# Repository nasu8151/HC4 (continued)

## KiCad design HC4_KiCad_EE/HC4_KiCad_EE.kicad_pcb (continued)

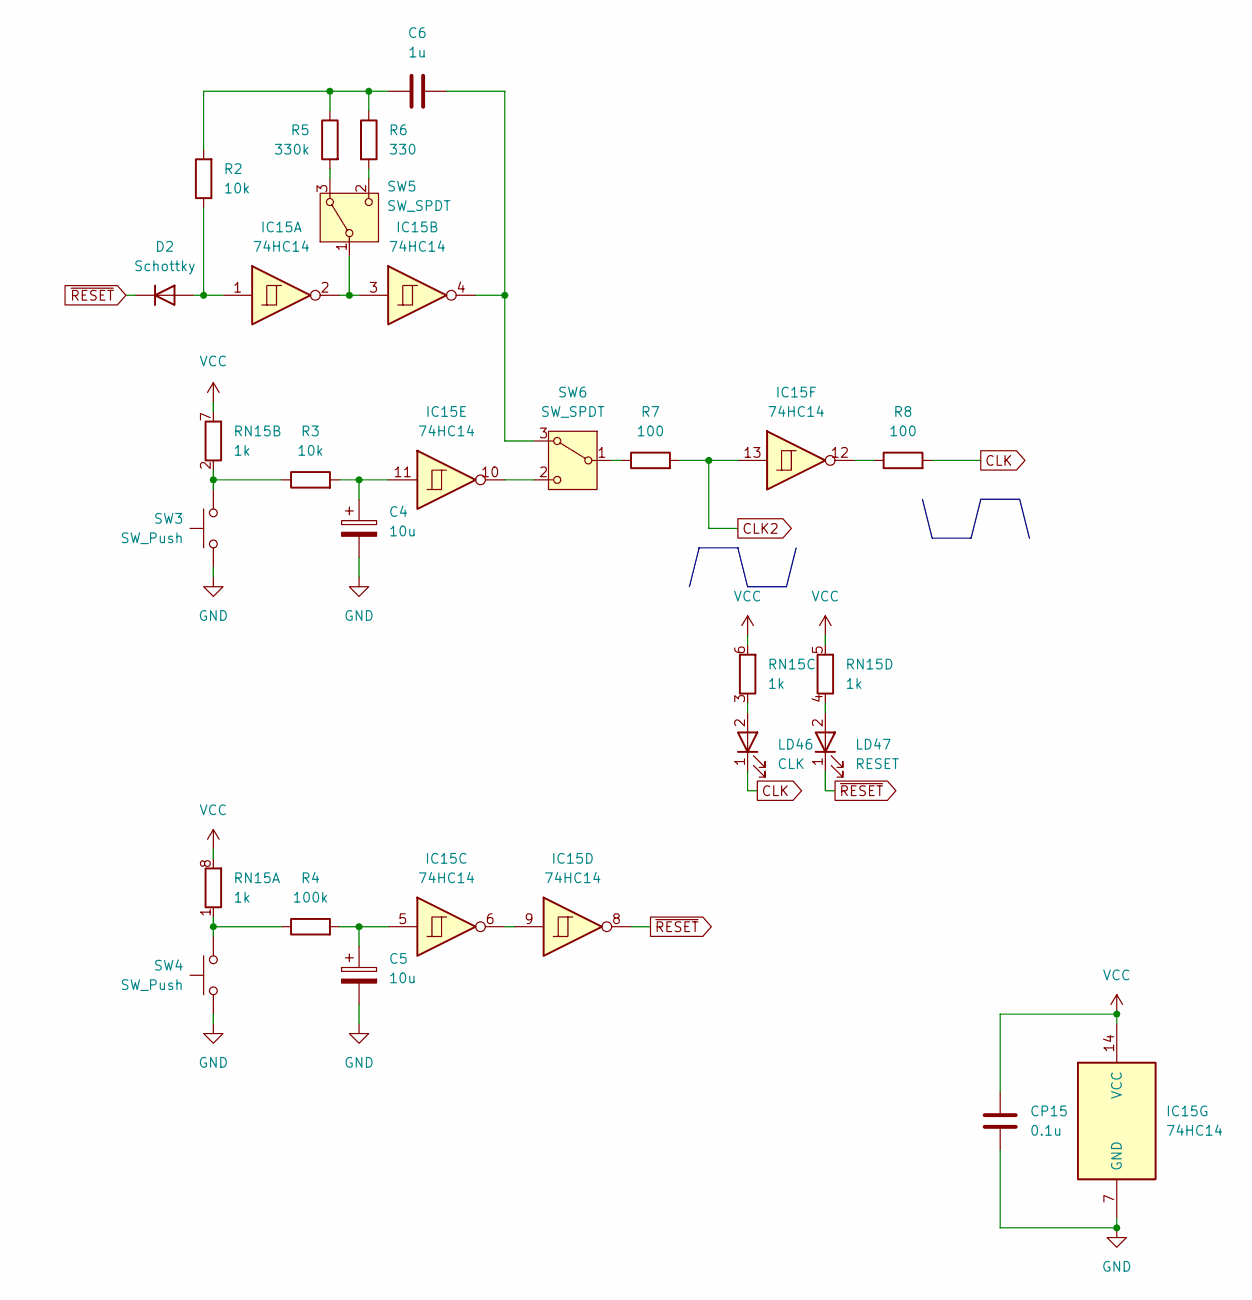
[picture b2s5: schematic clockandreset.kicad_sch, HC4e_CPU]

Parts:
C4, C5: 10u; CP_Radial_D5.0mm_P2.50mm
C6: 1u; C_Radial_D5.0mm_H5.0mm_P2.00mm
CP15: 0.1u; C_0603_1608Metric; LCSC PN C14663
D2: Schottky; D_SOD-323_HandSoldering
IC15: 74HC14; SO-14_5.3x10.2mm_P1.27mm
LD46: CLK; LED_D5.0mm
LD47: RESET; LED_D5.0mm
R2, R3: 10k; R_0603_1608Metric; LCSC PN C25804
R4: 100k; R_0603_1608Metric; LCSC PN C25803
R5: 330k; R_0603_1608Metric; LCSC PN C23137
R6: 330; R_0603_1608Metric; LCSC PN C23151
R7, R8: 100; R_0603_1608Metric; LCSC PN C22775
RN15: 1k; R_Array_Convex_4x0603; LCSC PN C20197
SW3, SW4: SW_Push; SW_PUSH_6mm
SW5, SW6: SW_SPDT; SW_Slide-03_Wuerth-WS-SLTV_10x2.5x6.4_P2.54mm

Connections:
CLK: LD46.1 (K_1), R8.2; also elsewhere on the board
CLK2: IC15.13, R7.2; also elsewhere on the board
GND: C4.2, C5.2, CP15.2, IC15.7 (GND), SW3.1, SW4.1; also elsewhere on the board
unnamed: C4.1, IC15.11, R3.2
unnamed: C5.1, IC15.5, R4.2
unnamed: C6.1, R2.2, R5.1, R6.1
unnamed: D2.2 (A), IC15.1, R2.1
unnamed: IC15.6, IC15.9
unnamed: IC15.12, R8.1
unnamed: R4.1, RN15.1 (R1.1), SW4.2
unnamed: R3.1, RN15.2 (R2.1), SW3.2
unnamed: LD46.2, RN15.3 (R3.1)
unnamed: LD47.2, RN15.4 (R4.1)
unnamed: R5.2, SW5.3 (A)
unnamed: IC15.2, IC15.3, SW5.1 (B)
unnamed: R6.2, SW5.2 (C)
unnamed: C6.2, IC15.4, SW6.3 (A)
unnamed: R7.1, SW6.1 (B)
unnamed: IC15.10, SW6.2 (C)
VCC: CP15.1, IC15.14 (VCC), RN15.5 (R4.2), RN15.6 (R3.2), RN15.7 (R2.2), RN15.8 (R1.2); also elsewhere on the board
~RESET: D2.1 (K), IC15.8, LD47.1 (K_1); also elsewhere on the board

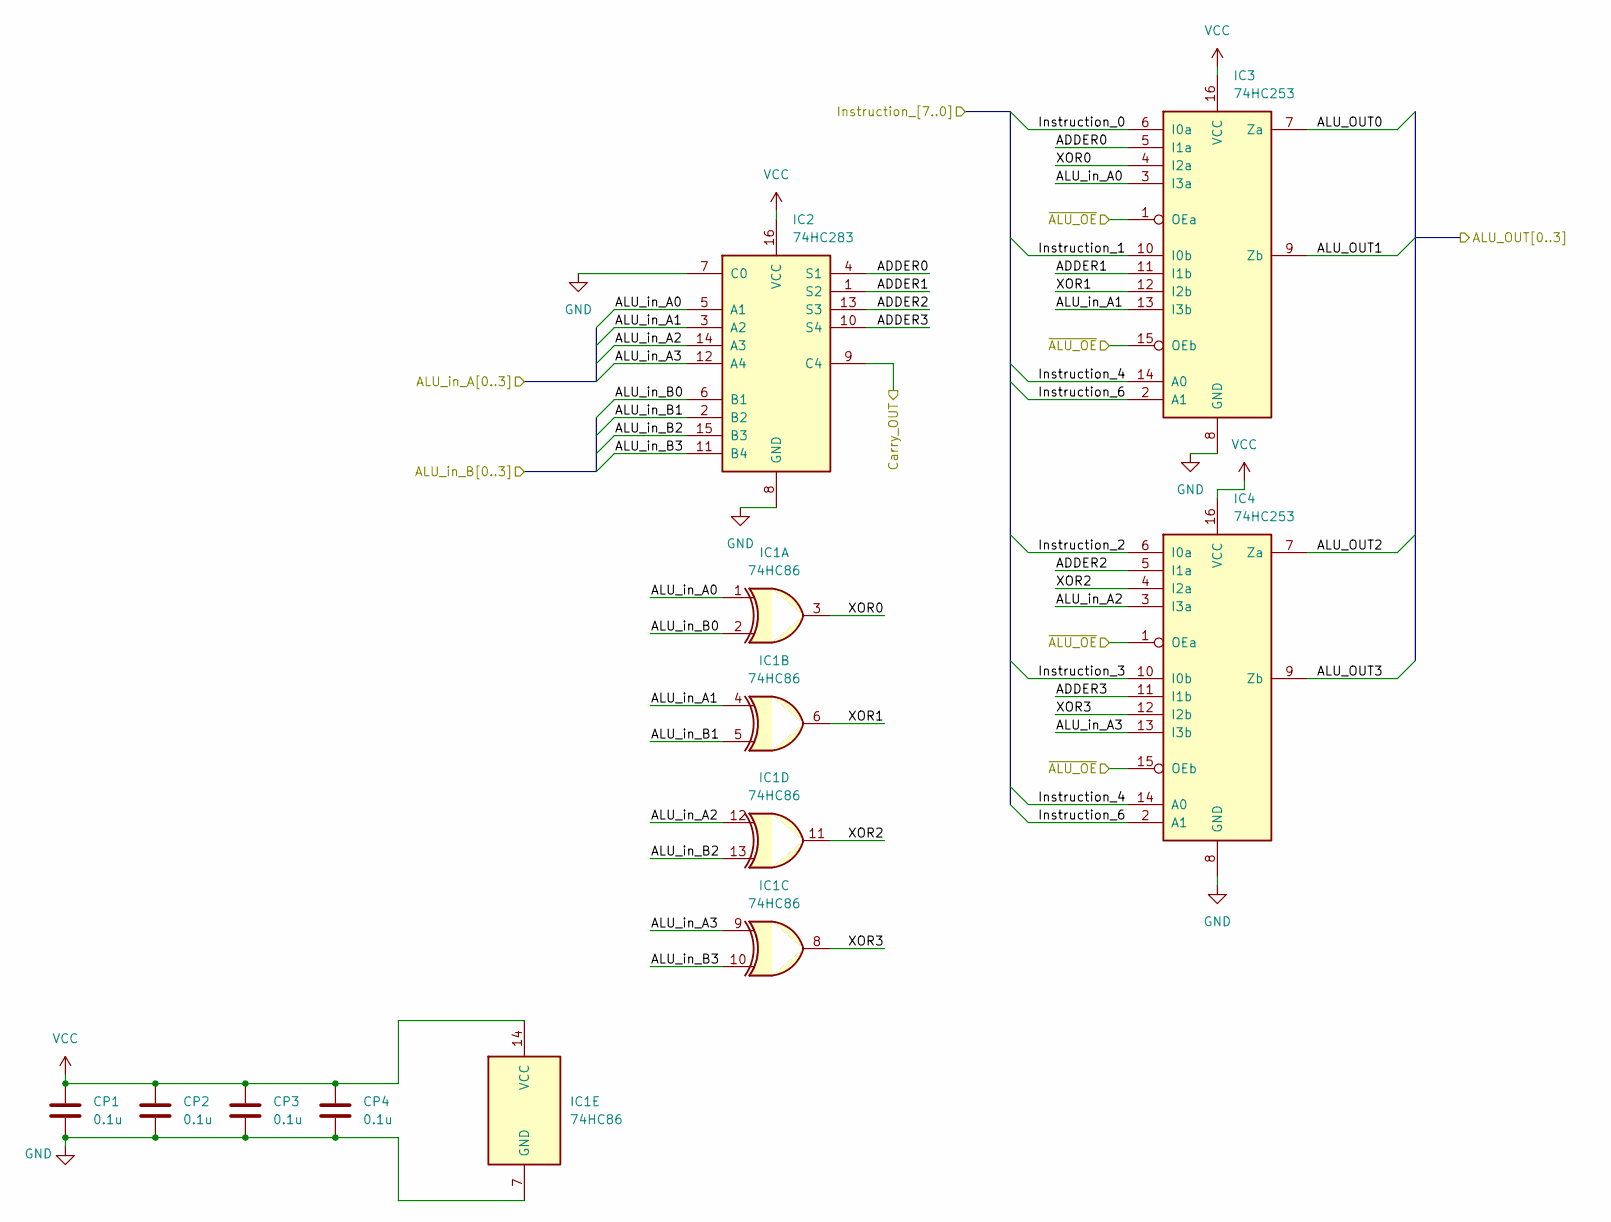
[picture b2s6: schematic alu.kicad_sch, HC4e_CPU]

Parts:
CP1, CP2, CP3, CP4: 0.1u; C_0603_1608Metric; LCSC PN C14663
IC1: 74HC86; SO-14_5.3x10.2mm_P1.27mm
IC2: 74HC283; SO-16_5.3x10.2mm_P1.27mm
IC3, IC4: 74HC253; SO-16_5.3x10.2mm_P1.27mm

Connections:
/ALU/ADDER0: IC2.4 (S1), IC3.5 (I1a)
/ALU/ADDER1: IC2.1 (S2), IC3.11 (I1b)
/ALU/ADDER2: IC2.13 (S3), IC4.5 (I1a)
/ALU/ADDER3: IC2.10 (S4), IC4.11 (I1b)
/ALU/ALU_OUT0: IC3.7 (Za); also elsewhere on the board
/ALU/ALU_OUT1: IC3.9 (Zb); also elsewhere on the board
/ALU/ALU_OUT2: IC4.7 (Za); also elsewhere on the board
/ALU/ALU_OUT3: IC4.9 (Zb); also elsewhere on the board
/ALU/ALU_in_A0: IC1.1, IC2.5 (A1), IC3.3 (I3a); also elsewhere on the board
/ALU/ALU_in_A1: IC1.4, IC2.3 (A2), IC3.13 (I3b); also elsewhere on the board
/ALU/ALU_in_A2: IC1.12, IC2.14 (A3), IC4.3 (I3a); also elsewhere on the board
/ALU/ALU_in_A3: IC1.9, IC2.12 (A4), IC4.13 (I3b); also elsewhere on the board
/ALU/ALU_in_B0: IC1.2, IC2.6 (B1); also elsewhere on the board
/ALU/ALU_in_B1: IC1.5, IC2.2 (B2); also elsewhere on the board
/ALU/ALU_in_B2: IC1.13, IC2.15 (B3); also elsewhere on the board
/ALU/ALU_in_B3: IC1.10, IC2.11 (B4); also elsewhere on the board
/ALU/Carry_OUT: IC2.9 (C4); also elsewhere on the board
/ALU/Instruction_4: IC3.14 (A0), IC4.14 (A0); also elsewhere on the board
/ALU/Instruction_6: IC3.2 (A1), IC4.2 (A1); also elsewhere on the board
/ALU/XOR0: IC1.3, IC3.4 (I2a)
/ALU/XOR1: IC1.6, IC3.12 (I2b)
/ALU/XOR2: IC1.11, IC4.4 (I2a)
/ALU/XOR3: IC1.8, IC4.12 (I2b)
/Instruction Decoder/READ: IC3.1 (OEa), IC3.15 (OEb), IC4.1 (OEa), IC4.15 (OEb); also elsewhere on the board
GND: CP1.2, CP2.2, CP3.2, CP4.2, IC1.7 (GND), IC2.7 (C0), IC2.8 (GND), IC3.8 (GND), IC4.8 (GND); also elsewhere on the board
VCC: CP1.1, CP2.1, CP3.1, CP4.1, IC1.14 (VCC), IC2.16 (VCC), IC3.16 (VCC), IC4.16 (VCC); also elsewhere on the board

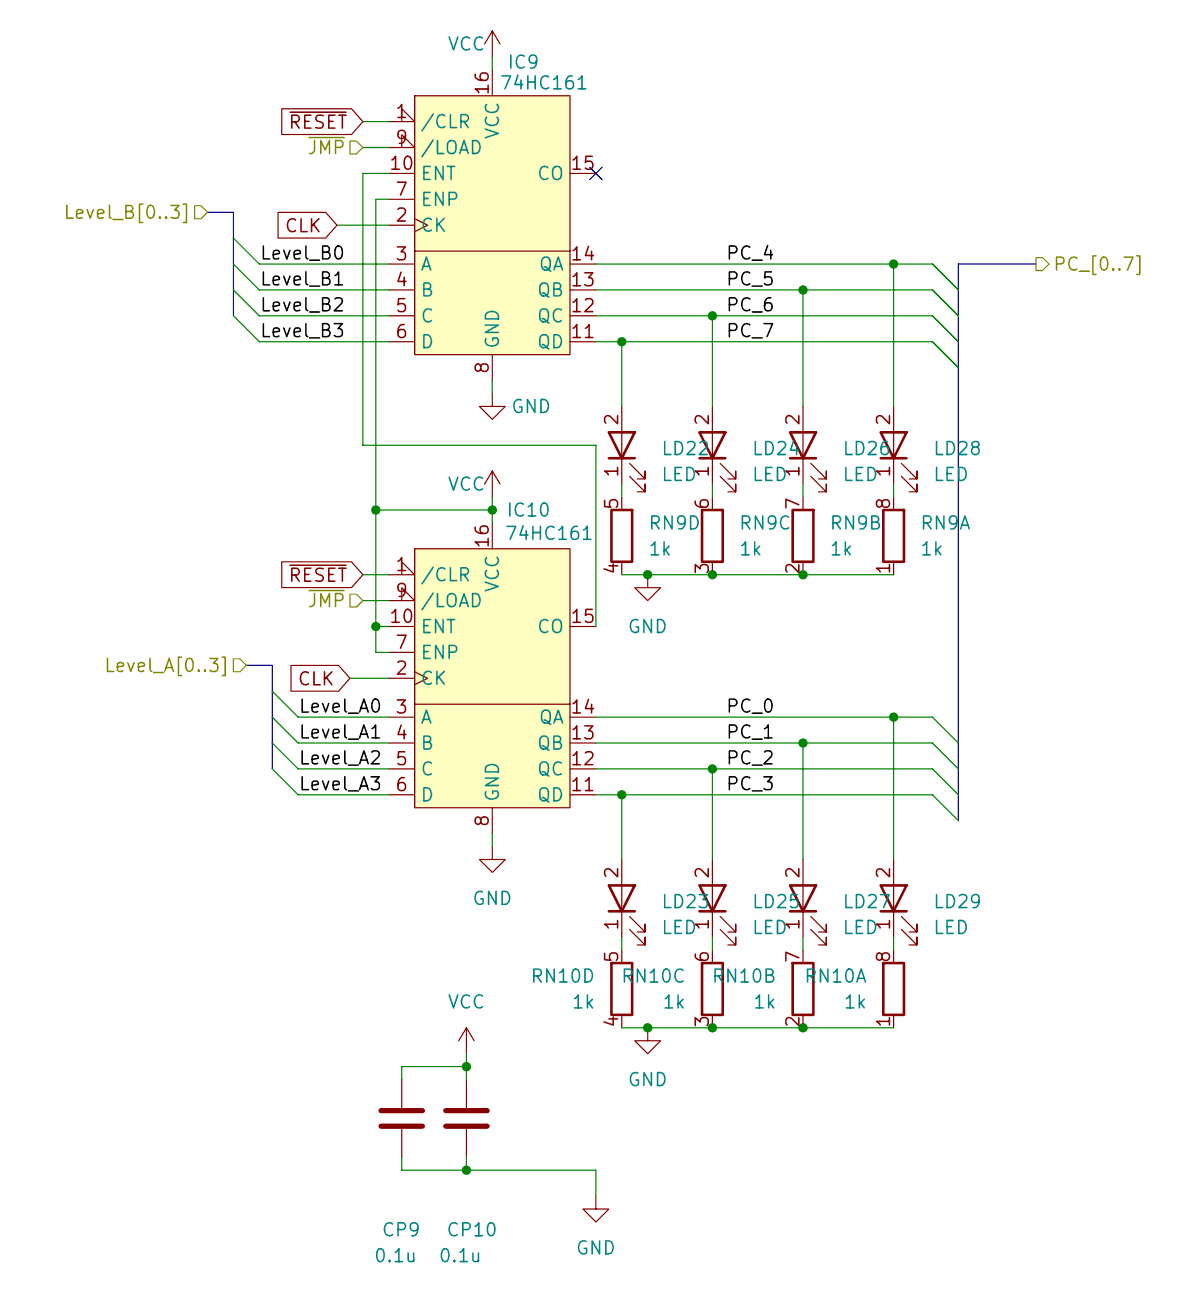
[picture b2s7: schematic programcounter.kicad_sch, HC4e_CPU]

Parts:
CP9, CP10: 0.1u; C_0603_1608Metric; LCSC PN C14663
IC9, IC10: 74HC161; SO-16_5.3x10.2mm_P1.27mm
LD22, LD23, LD24, LD25, LD26, LD27, LD28, LD29: LED; LED_Rectangular_W5.0mm_H2.0mm
RN9, RN10: 1k; R_Array_Convex_4x0603; LCSC PN C20197

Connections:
/ALU/ALU_in_A0: IC10.3 (A); also elsewhere on the board
/ALU/ALU_in_A1: IC10.4 (B); also elsewhere on the board
/ALU/ALU_in_A2: IC10.5 (C); also elsewhere on the board
/ALU/ALU_in_A3: IC10.6 (D); also elsewhere on the board
/ALU/ALU_in_B0: IC9.3 (A); also elsewhere on the board
/ALU/ALU_in_B1: IC9.4 (B); also elsewhere on the board
/ALU/ALU_in_B2: IC9.5 (C); also elsewhere on the board
/ALU/ALU_in_B3: IC9.6 (D); also elsewhere on the board
/Instruction Decoder/~JMP: IC9.9 (/LOAD), IC10.9 (/LOAD); also elsewhere on the board
/Program Counter/PC_0: IC10.14 (QA), LD29.2; also elsewhere on the board
/Program Counter/PC_1: IC10.13 (QB), LD27.2; also elsewhere on the board
/Program Counter/PC_2: IC10.12 (QC), LD25.2; also elsewhere on the board
/Program Counter/PC_3: IC10.11 (QD), LD23.2; also elsewhere on the board
/Program Counter/PC_4: IC9.14 (QA), LD28.2; also elsewhere on the board
/Program Counter/PC_5: IC9.13 (QB), LD26.2; also elsewhere on the board
/Program Counter/PC_6: IC9.12 (QC), LD24.2; also elsewhere on the board
/Program Counter/PC_7: IC9.11 (QD), LD22.2; also elsewhere on the board
CLK: IC9.2 (CK), IC10.2 (CK); also elsewhere on the board
GND: CP9.2, CP10.2, IC9.8 (GND), IC10.8 (GND), RN9.1 (R1.1), RN9.2 (R2.1), RN9.3 (R3.1), RN9.4 (R4.1), RN10.1 (R1.1), RN10.2 (R2.1), RN10.3 (R3.1), RN10.4 (R4.1); also elsewhere on the board
unnamed: IC9.10 (ENT), IC10.15 (CO)
unnamed: LD22.1 (K_1), RN9.5 (R4.2)
unnamed: LD23.1 (K_1), RN10.5 (R4.2)
unnamed: LD24.1 (K_1), RN9.6 (R3.2)
unnamed: LD25.1 (K_1), RN10.6 (R3.2)
unnamed: LD26.1 (K_1), RN9.7 (R2.2)
unnamed: LD27.1 (K_1), RN10.7 (R2.2)
unnamed: LD28.1 (K_1), RN9.8 (R1.2)
unnamed: LD29.1 (K_1), RN10.8 (R1.2)
VCC: CP9.1, CP10.1, IC9.7 (ENP), IC9.16 (VCC), IC10.7 (ENP), IC10.10 (ENT), IC10.16 (VCC); also elsewhere on the board
~RESET: IC9.1 (/CLR), IC10.1 (/CLR); also elsewhere on the board

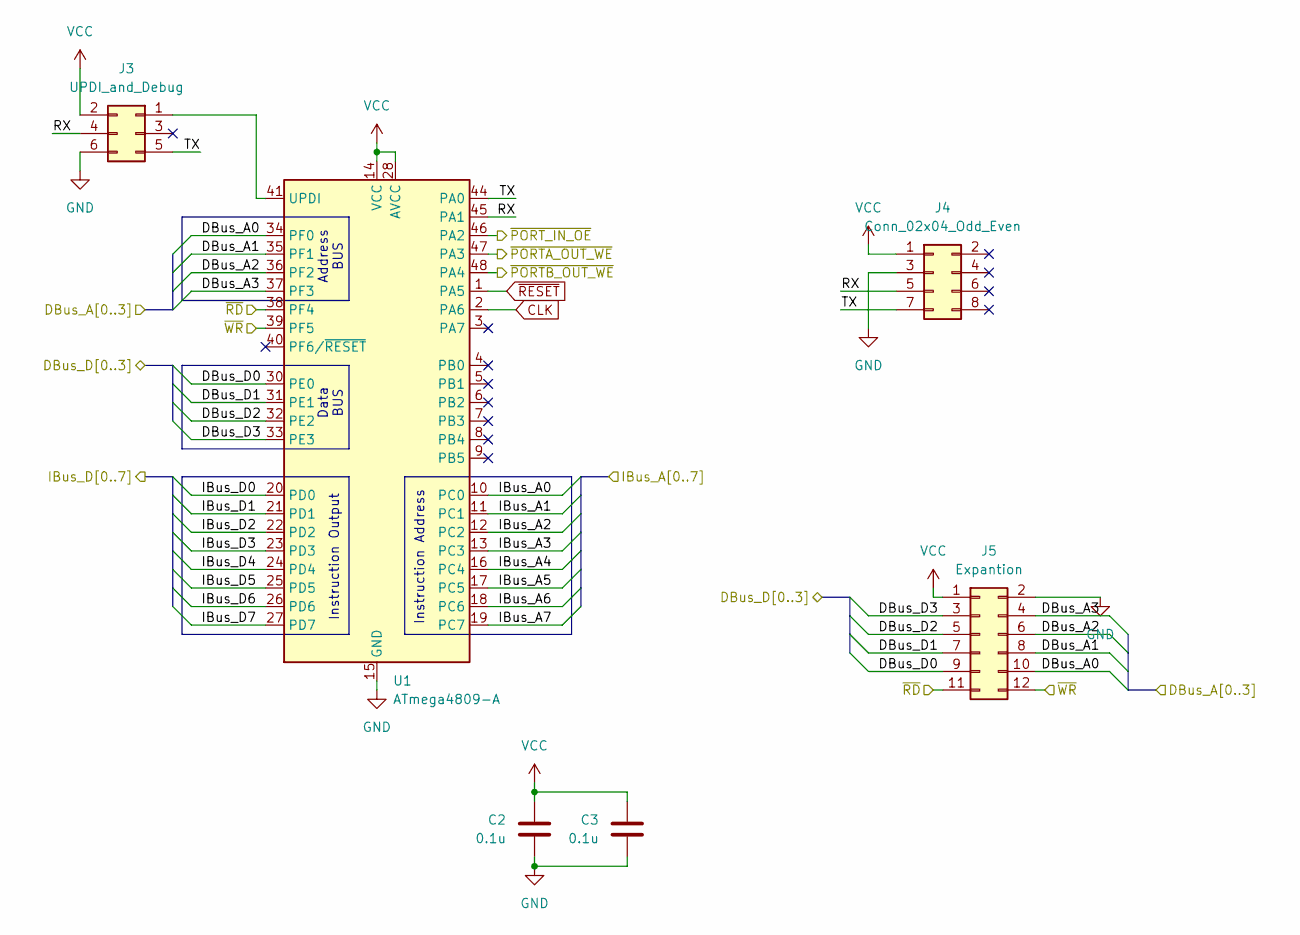
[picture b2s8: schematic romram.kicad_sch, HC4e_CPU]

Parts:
C2, C3: 0.1u; C_0603_1608Metric; LCSC PN C14663
J3: UPDI_and_Debug; PinHeader_2x03_P2.54mm_Vertical
J4: Conn_02x04_Odd_Even; PinHeader_2x04_P2.54mm_Vertical
J5: Expantion; PinHeader_2x06_P2.54mm_Vertical
U1: ATmega4809-A; TQFP-48_7x7mm_P0.5mm; LCSC PN C1340574

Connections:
/ALU/ALU_OUT0: J5.9, U1.30 (PE0); also elsewhere on the board
/ALU/ALU_OUT1: J5.7, U1.31 (PE1); also elsewhere on the board
/ALU/ALU_OUT2: J5.5, U1.32 (PE2); also elsewhere on the board
/ALU/ALU_OUT3: J5.3, U1.33 (PE3); also elsewhere on the board
/ALU/Instruction_4: U1.24 (PD4); also elsewhere on the board
/ALU/Instruction_5: U1.25 (PD5); also elsewhere on the board
/ALU/Instruction_6: U1.26 (PD6); also elsewhere on the board
/ALU/Instruction_7: U1.27 (PD7); also elsewhere on the board
/Data BUS/~IN_PORT_OE: U1.46 (PA2); also elsewhere on the board
/Data BUS/~PORTA_OUT_WE: U1.47 (PA3); also elsewhere on the board
/Data BUS/~PORTB_OUT_WE: U1.48 (PA4); also elsewhere on the board
/Instruction Decoder/~RAM_RD: J5.11, U1.38 (PF4); also elsewhere on the board
/Instruction Decoder/~RAM_WR: J5.12, U1.39 (PF5); also elsewhere on the board
/Program Counter/PC_0: U1.10 (PC0); also elsewhere on the board
/Program Counter/PC_1: U1.11 (PC1); also elsewhere on the board
/Program Counter/PC_2: U1.12 (PC2); also elsewhere on the board
/Program Counter/PC_3: U1.13 (PC3); also elsewhere on the board
/Program Counter/PC_4: U1.16 (PC4); also elsewhere on the board
/Program Counter/PC_5: U1.17 (PC5); also elsewhere on the board
/Program Counter/PC_6: U1.18 (PC6); also elsewhere on the board
/Program Counter/PC_7: U1.19 (PC7); also elsewhere on the board
/ROM_RAM/RX: J3.4, J4.5, U1.45 (PA1)
/ROM_RAM/TX: J3.5, J4.7, U1.44 (PA0)
CLK: U1.2 (PA6); also elsewhere on the board
GND: C2.2, C3.2, J3.6, J4.3, J5.2, U1.15 (GND), U1.29 (GND), U1.43 (GND); also elsewhere on the board
unnamed: J3.1, U1.41 (UPDI)
VCC: C2.1, C3.1, J3.2, J4.1, J5.1, U1.14 (VCC), U1.28 (AVCC), U1.42 (VCC); also elsewhere on the board
~RESET: U1.1 (PA5); also elsewhere on the board

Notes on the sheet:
Data BUS
Instruction Address
Instruction Output
Address BUS

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
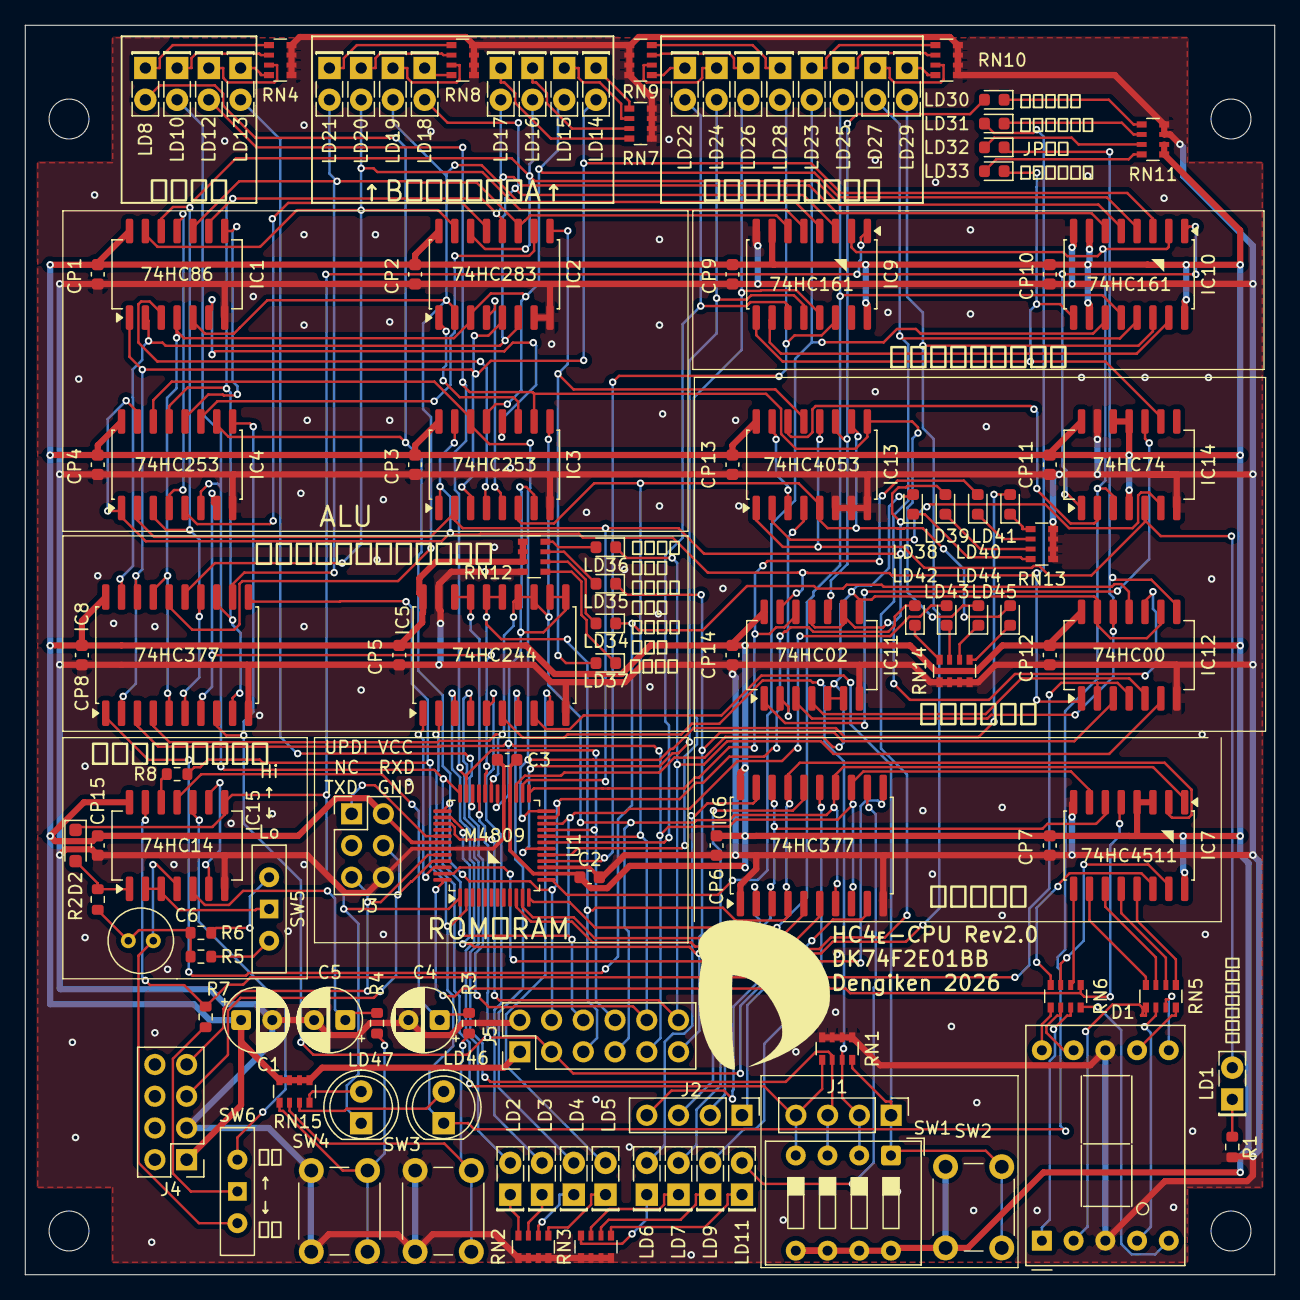
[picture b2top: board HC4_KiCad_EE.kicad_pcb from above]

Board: 2 copper layers, 100.0 x 100.0 mm, 124 parts (0 on the bottom side), 155 nets.

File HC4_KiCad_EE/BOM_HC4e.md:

| Reference    | Value               | Qty | Remarks                            |
|--------------|---------------------|-----|------------------------------------|
| C1           | 100u                | 1   |                                    |
| C2,C3,CP1-15 | 0.1u                | 17  | SMT 1608                           |
| C4,C5        | 10u                 | 2   |                                    |
| C6           | 1u                  | 1   | Use unipolar type                  |
| D1           | 7-Segment           | 1   | C-551SRD or equipment              |
| D2           | Schottky            | 1   | Switching diode in SOD-323 package |
| IC1,IC12     | 74HC00              | 2   | Use SOP package (D or *F)          |
| IC2          | 74HC283             | 1   | Use SOP package (D or *F)          |
| IC3,IC4      | 74HC253             | 2   | Use SOP package (D or *F)          |
| IC5          | 74HC244             | 1   | Use TSSOP package (PW)             |
| IC6,IC8      | 74HC377             | 2   | Use TSSOP package (PW)             |
| IC7          | 74HC4511            | 1   | Use SOP package (D or *F)          |
| IC9,IC10     | 74HC161             | 2   | Use SOP package (D or *F)          |
| IC11         | 74HC02              | 1   | Use SOP package (D or *F)          |
| IC13         | 74HC4053            | 1   | Use SOP package (D or *F)          |
| IC14         | 74HC74              | 1   | Use SOP package (D or *F)          |
| IC15         | 74HC14              | 1   | Use SOP package (D or *F)          |
| J1,J2        | Port                | 2   | Pinsocket_1x4                      |
| J3           | UPDI_and_Debug      | 1   | Pinheader_2x3                      |
| J4           | Conn_02x04_Odd_Even | 1   | USB-UART                           |
| J5           | Expantion           | 1   | Pinheader_2x5                      |
| LD1-29       | LED                 | 29  | 2x5mm Rectangler                   |
| LD30-45      | Chip                | 16  | SMT 1608                           |
| LD46         | CLK                 | 1   | D5mm, Yellow                       |
| LD47         | RESET               | 1   | D5mm, Red                          |
| R1           | 1k                  | 1   | SMT 1608                           |
| R2           | 10k                 | 1   | SMT 1608                           |
| R3           | 100k                | 1   | SMT 1608                           |
| R4           | 390k                | 1   | SMT 1608                           |
| R5           | 390                 | 1   | SMT 1608                           |
| R6,R7        | 100                 | 2   | SMT 1608                           |
| RN1          | 10k                 | 1   | Resistor array SMT 3216            |
| RN2-15       | 1k                  | 14  | Resistor array SMT 3216            |
| SW1          | SW_DIP_x04          | 1   |                                    |
| SW2,SW3,SW4  | SW_Push             | 3   |                                    |
| SW5,SW6      | SW_SPDT             | 2   |                                    |
| U1           | ATmega4809-AU       | 1   | or AVR32DB48                       |

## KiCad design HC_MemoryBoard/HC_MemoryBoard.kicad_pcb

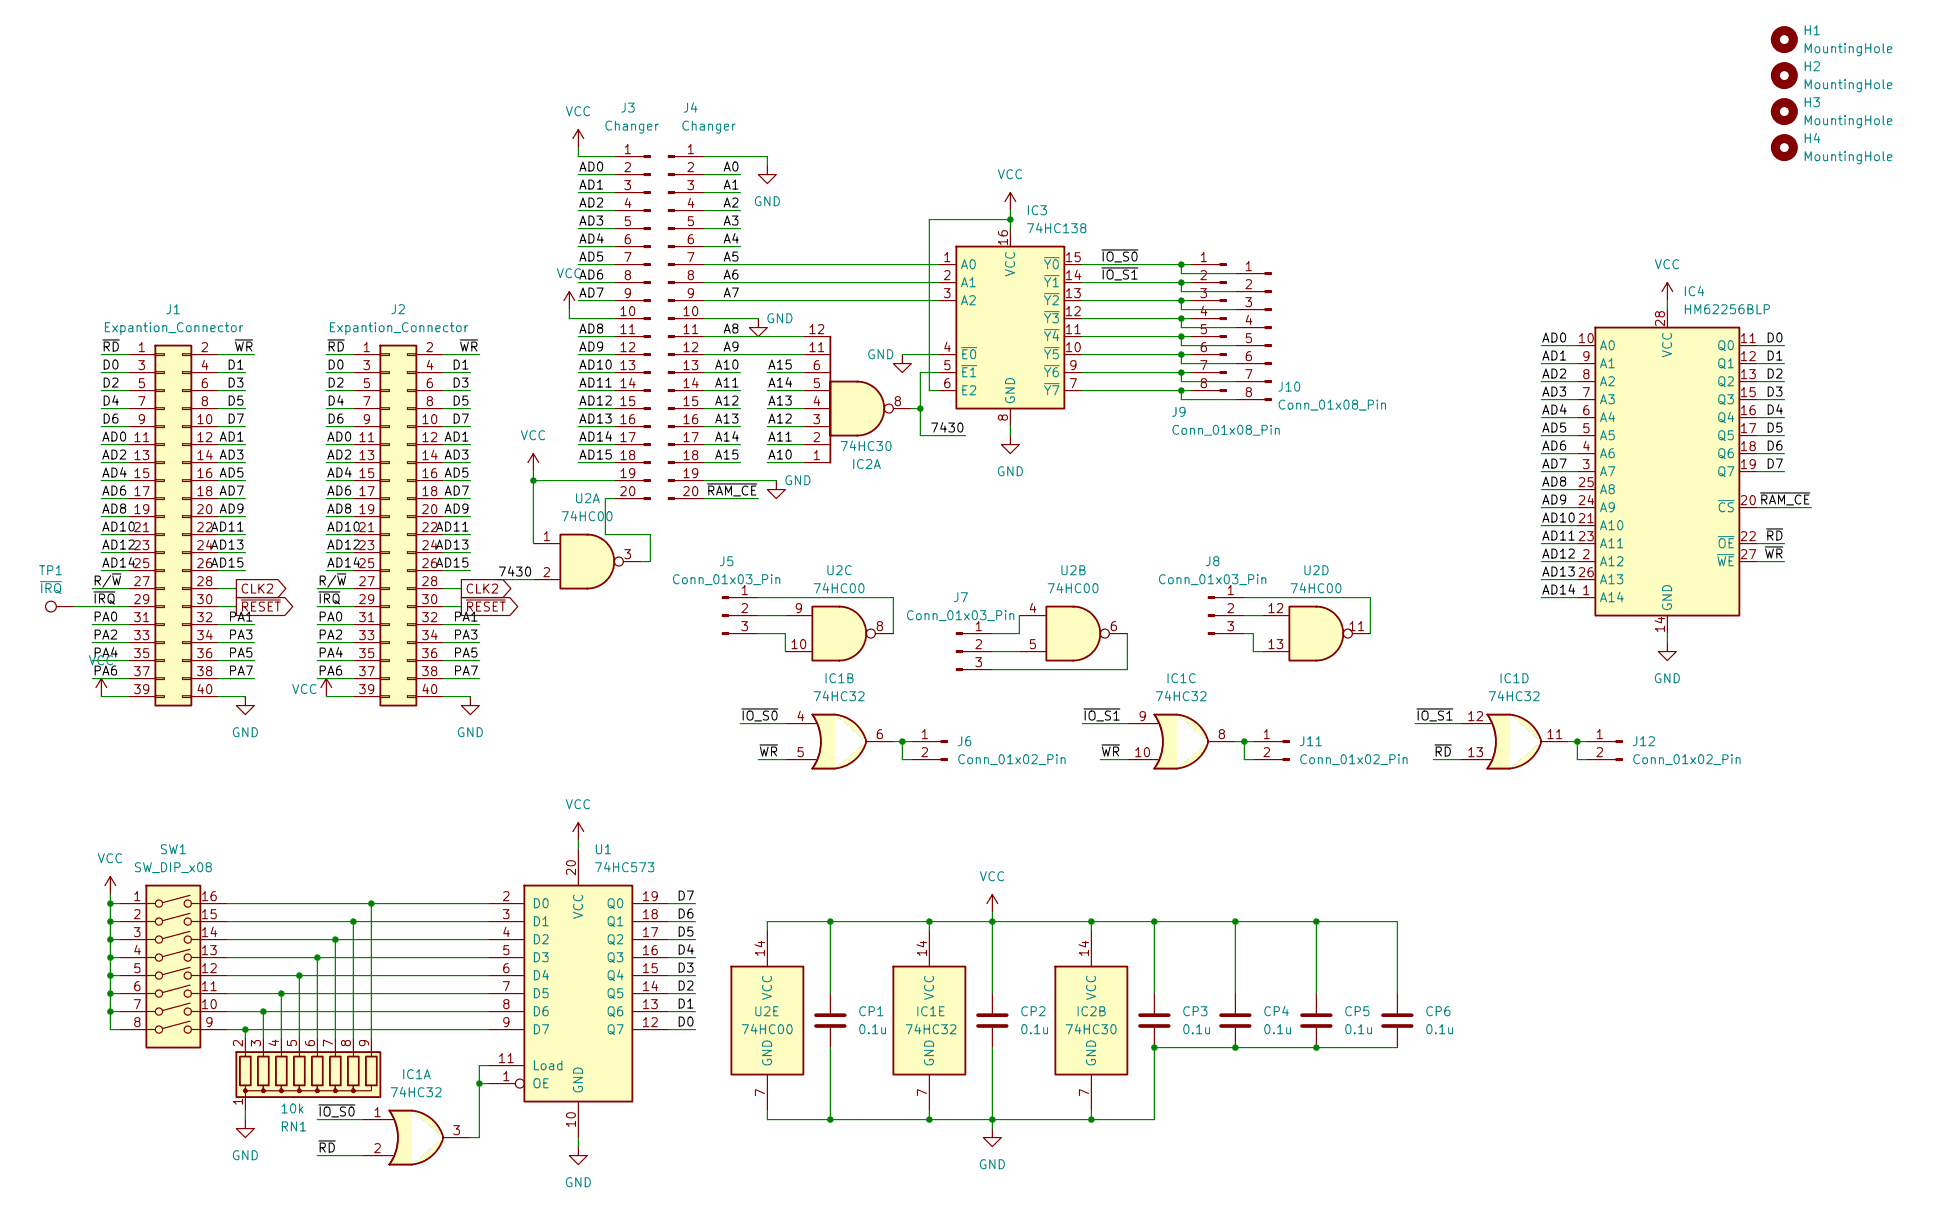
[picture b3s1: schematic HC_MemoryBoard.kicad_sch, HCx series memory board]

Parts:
CP1, CP2, CP3, CP4, CP5, CP6: 0.1u; C_Disc_D3.0mm_W1.6mm_P2.50mm
H1, H2, H3, H4: MountingHole; MountingHole_3.2mm_M3
IC1: 74HC32; DIP-14_W7.62mm
IC2: 74HC30; DIP-14_W7.62mm
IC3: 74HC138; DIP-16_W7.62mm
IC4: HM62256BLP; DIP-28_W15.24mm
J1, J2: Expantion_Connector; PinHeader_2x20_P2.54mm_Vertical
J3, J4: Changer; PinSocket_1x20_P2.54mm_Vertical
J5, J7, J8: Conn_01x03_Pin; PinSocket_1x03_P2.54mm_Vertical
J6, J11, J12: Conn_01x02_Pin; PinHeader_1x02_P2.54mm_Vertical
J9, J10: Conn_01x08_Pin; PinHeader_1x08_P2.54mm_Vertical
RN1: 10k; R_Array_SIP9
SW1: SW_DIP_x08; SW_DIP_SPSTx08_Slide_9.78x22.5mm_W7.62mm_P2.54mm
TP1: ~{IRQ}; PinHeader_1x01_P2.54mm_Vertical
U1: 74HC573; DIP-20_W7.62mm
U2: 74HC00; DIP-14_W7.62mm

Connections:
/7430: IC2.8, IC3.5 (~E1), U2.2
/A0: J4.2
/A1: J4.3
/A2: J4.4
/A3: J4.5
/A4: J4.6
/A5: IC3.1 (A0), J4.7
/A6: IC3.2 (A1), J4.8
/A7: IC3.3 (A2), J4.9
/A8: IC2.12, J4.11
/A9: IC2.11, J4.12
/A10: IC2.1, J4.13
/A11: IC2.2, J4.14
/A12: IC2.3, J4.15
/A13: IC2.4, J4.16
/A14: IC2.5, J4.17
/A15: IC2.6, J4.18
/AD0: IC4.10 (A0), J1.11, J2.11, J3.2
/AD1: IC4.9 (A1), J1.12, J2.12, J3.3
/AD2: IC4.8 (A2), J1.13, J2.13, J3.4
/AD3: IC4.7 (A3), J1.14, J2.14, J3.5
/AD4: IC4.6 (A4), J1.15, J2.15, J3.6
/AD5: IC4.5 (A5), J1.16, J2.16, J3.7
/AD6: IC4.4 (A6), J1.17, J2.17, J3.8
/AD7: IC4.3 (A7), J1.18, J2.18, J3.9
/AD8: IC4.25 (A8), J1.19, J2.19, J3.11
/AD9: IC4.24 (A9), J1.20, J2.20, J3.12
/AD10: IC4.21 (A10), J1.21, J2.21, J3.13
/AD11: IC4.23 (A11), J1.22, J2.22, J3.14
/AD12: IC4.2 (A12), J1.23, J2.23, J3.15
/AD13: IC4.26 (A13), J1.24, J2.24, J3.16
/AD14: IC4.1 (A14), J1.25, J2.25, J3.17
/AD15: J1.26, J2.26, J3.18
/D0: IC4.11 (Q0), J1.3, J2.3, U1.12 (Q7)
/D1: IC4.12 (Q1), J1.4, J2.4, U1.13 (Q6)
/D2: IC4.13 (Q2), J1.5, J2.5, U1.14 (Q5)
/D3: IC4.15 (Q3), J1.6, J2.6, U1.15 (Q4)
/D4: IC4.16 (Q4), J1.7, J2.7, U1.16 (Q3)
/D5: IC4.17 (Q5), J1.8, J2.8, U1.17 (Q2)
/D6: IC4.18 (Q6), J1.9, J2.9, U1.18 (Q1)
/D7: IC4.19 (Q7), J1.10, J2.10, U1.19 (Q0)
/PA0: J1.31, J2.31
/PA1: J1.32, J2.32
/PA2: J1.33, J2.33
/PA3: J1.34, J2.34
/PA4: J1.35, J2.35
/PA5: J1.36, J2.36
/PA6: J1.37, J2.37
/PA7: J1.38, J2.38
/R/~W: J1.27, J2.27
/~IO_S0: IC1.1, IC1.4, IC3.15 (~Y0), J9.1, J10.1
/~IO_S1: IC1.9, IC1.12, IC3.14 (~Y1), J9.2, J10.2
/~IRQ: J1.29, J2.29, TP1.1
/~RAM_CE: IC4.20 (~CS), J4.20
/~RD: IC1.2, IC1.13, IC4.22 (~OE), J1.1, J2.1
/~WR: IC1.5, IC1.10, IC4.27 (~WE), J1.2, J2.2
CLK2: J1.28, J2.28
GND: CP1.2, CP2.2, CP3.2, CP4.2, CP5.2, CP6.2, IC1.7 (GND), IC2.7 (GND), IC3.4 (~E0), IC3.8 (GND), IC4.14 (GND), J1.40, J2.40, J4.1, J4.10, J4.19, RN1.1 (common), U1.10 (GND), U2.7 (GND)
unnamed: IC3.13 (~Y2), J9.3, J10.3
unnamed: IC3.12 (~Y3), J9.4, J10.4
unnamed: IC3.11 (~Y4), J9.5, J10.5
unnamed: IC3.10 (~Y5), J9.6, J10.6
unnamed: IC3.9 (~Y6), J9.7, J10.7
unnamed: IC3.7 (~Y7), J9.8, J10.8
unnamed: J3.20, U2.3
unnamed: J5.1, U2.8
unnamed: J5.2, U2.9
unnamed: J5.3, U2.10
unnamed: IC1.6, J6.1, J6.2
unnamed: J7.1, U2.4
unnamed: J7.2, U2.5
unnamed: J7.3, U2.6
unnamed: J8.1, U2.11
unnamed: J8.2, U2.12
unnamed: J8.3, U2.13
unnamed: IC1.8, J11.1, J11.2
unnamed: IC1.11, J12.1, J12.2
unnamed: RN1.2 (R1), SW1.9, U1.9 (D7)
unnamed: RN1.3 (R2), SW1.10, U1.8 (D6)
unnamed: RN1.4 (R3), SW1.11, U1.7 (D5)
unnamed: RN1.5 (R4), SW1.12, U1.6 (D4)
unnamed: RN1.6 (R5), SW1.13, U1.5 (D3)
unnamed: RN1.7 (R6), SW1.14, U1.4 (D2)
unnamed: RN1.8 (R7), SW1.15, U1.3 (D1)
unnamed: RN1.9 (R8), SW1.16, U1.2 (D0)
unnamed: IC1.3, U1.1 (OE), U1.11 (Load)
VCC: CP1.1, CP2.1, CP3.1, CP4.1, CP5.1, CP6.1, IC1.14 (VCC), IC2.14 (VCC), IC3.6 (E2), IC3.16 (VCC), IC4.28 (VCC), J1.39, J2.39, J3.1, J3.10, J3.19, SW1.1, SW1.2, SW1.3, SW1.4, SW1.5, SW1.6, SW1.7, SW1.8, U1.20 (VCC), U2.1, U2.14 (VCC)
~RESET: J1.30, J2.30

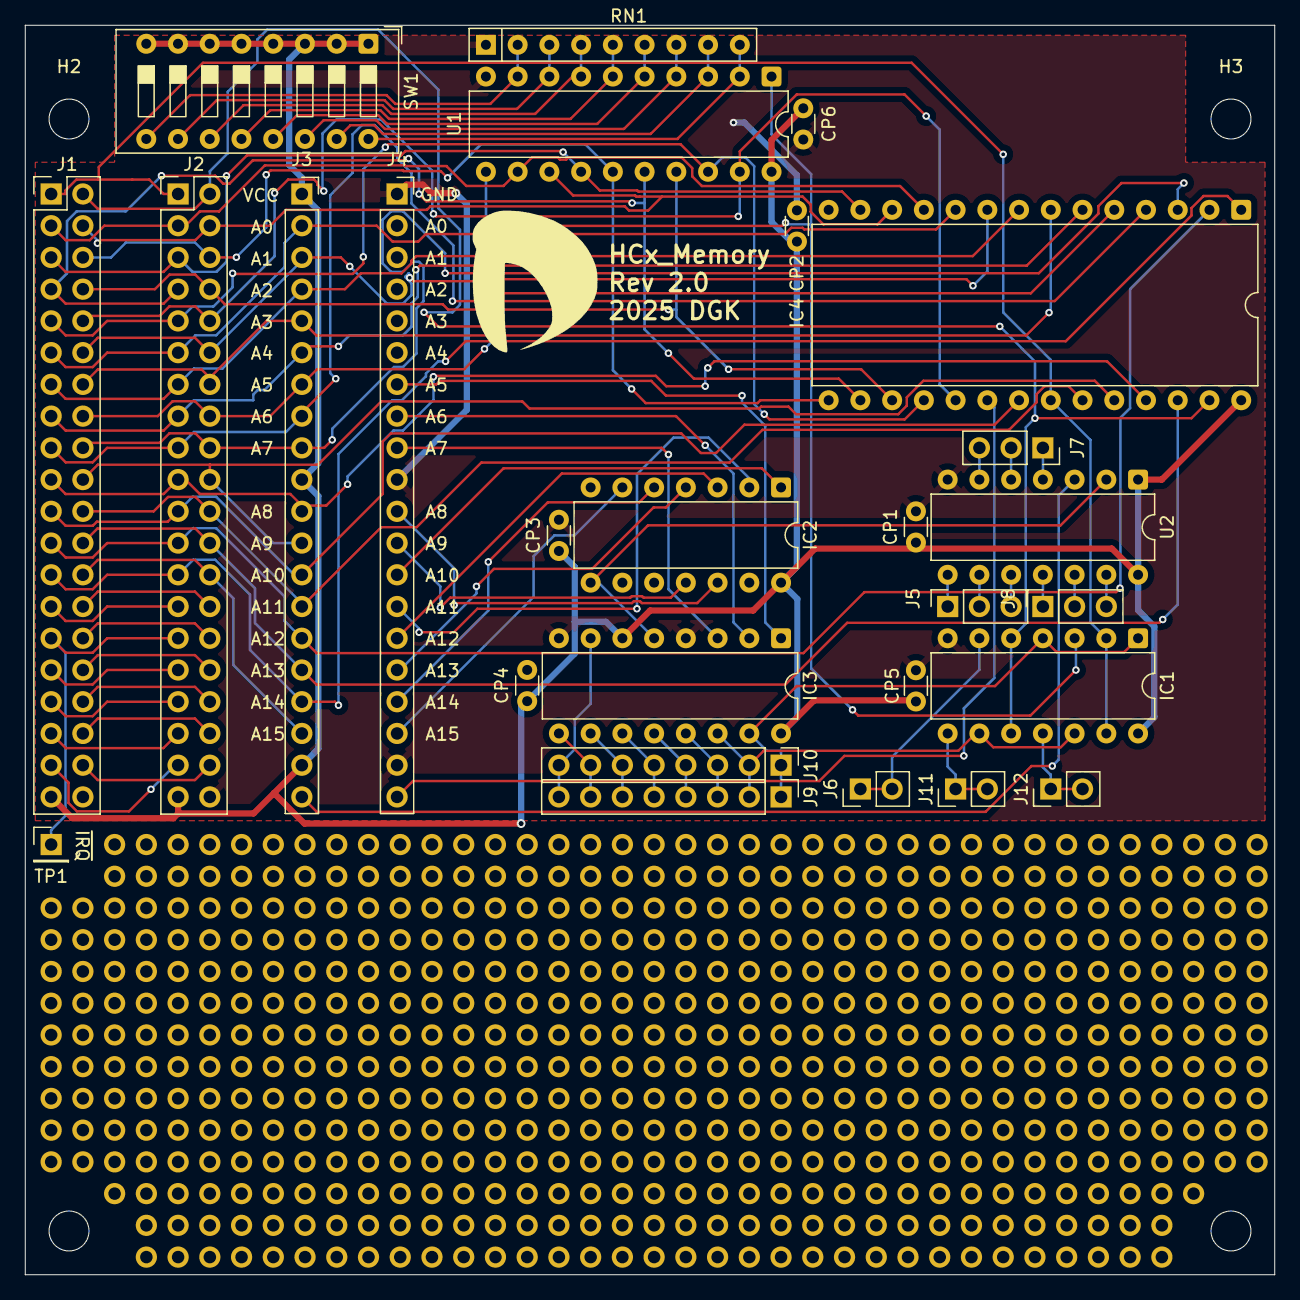
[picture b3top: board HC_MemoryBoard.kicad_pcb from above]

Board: 2 copper layers, 100.0 x 100.0 mm, 31 parts (0 on the bottom side), 83 nets.
